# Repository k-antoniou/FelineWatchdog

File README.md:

# 🐱 Feline Watchdog: Missing Cat Alert System

Feline Watchdog is an ESP32-based system designed to monitor the Wi-Fi connection between your cat's collar-mounted ESP32 device and your home network. If the Wi-Fi connection is lost, indicating that your cat may have wandered out of range, the system sends a notification to your iOS or Android device using the ntfy Linux tool.

## Overview

Have you ever worried about your cat wandering too far from home? Feline Watchdog provides peace of mind by alerting you when your cat goes missing. By monitoring the Wi-Fi connection between your cat's collar-mounted ESP32 device and your home network, Feline Watchdog can detect when your cat is out of range and send you an alert notification on your mobile device.

## 🔧 Prerequisites

- ESP32 microcontroller
- Raspberry Pi (Optional)
- Docker (if using Raspberry Pi)
- Router (if not using Raspberry Pi)

## Embedded System Configuration

<p align="center">
  <b>Two implementations of Embedded System Configuration</b>
</p>

### Option 1: With Raspberry Pi

1. **Setting Up a Wi-Fi Hotspot on Embedded System**

   - For detailed instructions on setting up a Wi-Fi hotspot on your embedded system, please refer to the [Wi-Fi Hotspot Setup Instructions](WiFi_hotspot.md).

   - Use the provided bash script using the **nmcli** tool to create a Wi-Fi hotspot on the Raspberry Pi. 
    ```bash
    bash create_hotspot.sh
    ```
    or
    ```bash
    ./create_hotspot.sh
    ```
  2. **Install Docker on your Raspberry Pi**
  ```bash
  sudo docker --version
  Docker version 20.10.21, build 20.10.21-0ubuntu1~18.04.3
  ```
  ```bash
  docker run \
    -v /var/cache/ntfy:/var/cache/ntfy \
    -v /etc/ntfy:/etc/ntfy \
    -p 80:80 \
    -itd \
    binwiederhier/ntfy \
      serve \
      --cache-file /var/cache/ntfy/cache.db
  ```
## 📡 ESP32 Configuration and Notification Setup

### Option 1: Using Raspberry Pi as a Wi-Fi Hotspot

1. **ESP32 Configuration**
   - Upload the `cat.ino` code to your ESP32.
   - The ESP32 will connect to the Wi-Fi hotspot created by the Raspberry Pi.
   - Once connected, the assigned IP address will be printed to the serial monitor.

2. **Raspberry Pi Monitoring and Notification**
   - The Raspberry Pi continuously monitors the connection status of the ESP32.
   - If the connection is lost, it triggers a notification using ntfy.

### Option 2: Direct Connection to Router

For a basic example of using NTFY with ESP boards, check out the [ntfy_on_a_chip repository](https://github.com/gergepalfi/ntfy_on_a_chip). It provides a foundational setup for communicating with the NTFY server and can be adapted for various projects, including this.

1. **Connect ESP32 Directly to Router**
   - Configure your ESP32 to connect directly to your home Wi-Fi network (router).

2. **ESP32 Configuration**
   - Upload the `cat.ino` code to your ESP32.
   - The ESP32 will connect to the specified Wi-Fi network and print the assigned IP address to the serial monitor.

3. **Notification Setup**
   - Set up ntfy or another notification service on a server or computer within your home network.
   - This service will monitor the connection status of the ESP32.
   - If the connection is lost, it triggers a notification using ntfy or a similar service.

### Notes
- Ensure that your network's firewall settings allow communication between the ESP32 and the notification service.
- Configure ntfy or your chosen notification service according to the service's documentation for optimal performance.

## 🔩 PCB Design

  ### Dual Power Sources: Li-ion Battery and USB

  This setup allows the ESP32 to be powered either by a Li-ion battery or directly from a USB source via a voltage regulator.

  ### Li-ion Battery Connection
  - The Li-ion battery is connected to the **BATT+** and **BATT-** terminals of the charger module.
  - **BATT+** from the charger module is connected to the 3.3V input of the ESP32 through a Schottky diode.
  - **BATT-** is connected to the GND of the ESP32.

  ### USB Power Connection (For Re-programming)
  - The 5V line from the USB is connected to the **VIN** of the voltage regulator.
  - **GND** from the USB is connected to the GND of the voltage regulator.
  - The 3.3V output of the voltage regulator is connected to the 3.3V input of the ESP32 through a Schottky diode.

  Screenshots from KiCad:

  Screenshots from Fusion 360:

  ### Important Notes
  - Schottky diodes are used to prevent backfeeding between the battery and USB power sources.

  ## 🏗️ 3D Design

  Screenshots from Fusion 360:

  ## 3D Printed Case

  Screenshots of the printed 3D case:

  ## To Do

  - [x] Implement notification functionality using ntfy for sending alerts to iOS or Android devices.
  - [x] Implementation without a middle point such as Raspberry Pi, but directly with a router and ESP32.
  - [ ] Lower power consumption.
  - [ ] Implement HTTP communication method for sending alerts to a designated endpoint.
  - [ ] Implement MQTT communication method for publishing messages to a specific topic on an MQTT broker.
  - [ ] Ensure seamless integration of these functionalities within a Docker container on the Raspberry Pi.
  - [ ] Document setup and configuration steps for each notification method.
  - [ ] Test and validate the system's functionality across different scenarios.
  - [ ] Gather feedback and suggestions from users for further enhancements.

  ## 🧑‍💻 Authors

  - 

  - 

  ## 👥 Contributors

  Contributions are welcome! Feel free to submit pull requests or open issues if you encounter any problems.

   ## 🙏 Acknowledgements

   - A special thanks to the [ntfy_on_a_chip](https://github.com/gergepalfi/ntfy_on_a_chip) repository by [Gerge](https://github.com/gergepalfi). The example code and documentation provided were instrumental in implementing the direct connection option for the Feline Watchdog project. The guidance on using NTFY with ESP boards and the detailed explanation of HTTPS communication enabled us to streamline our setup by connecting the ESP32 directly to a router without needing an intermediate server like a Raspberry Pi. Your work greatly facilitated our development process and contributed to the success of the Feline Watchdog system. Thank you!

   - We would also like to acknowledge the creators of the [ntfy](https://ntfy.sh) app. The app’s simplicity and functionality made it easy to send and receive notifications, which is a core feature of the Feline Watchdog system. The ability to integrate it seamlessly into our project greatly enhanced its effectiveness.

   ## 📜 License
   
   This project is licensed under the [GPLv3 License](https://opensource.org/licenses/GPL-3.0) - see the [LICENSE](LICENSE) file for details.

   - 

**Thank you for visiting FelineWatchdog!** ✨

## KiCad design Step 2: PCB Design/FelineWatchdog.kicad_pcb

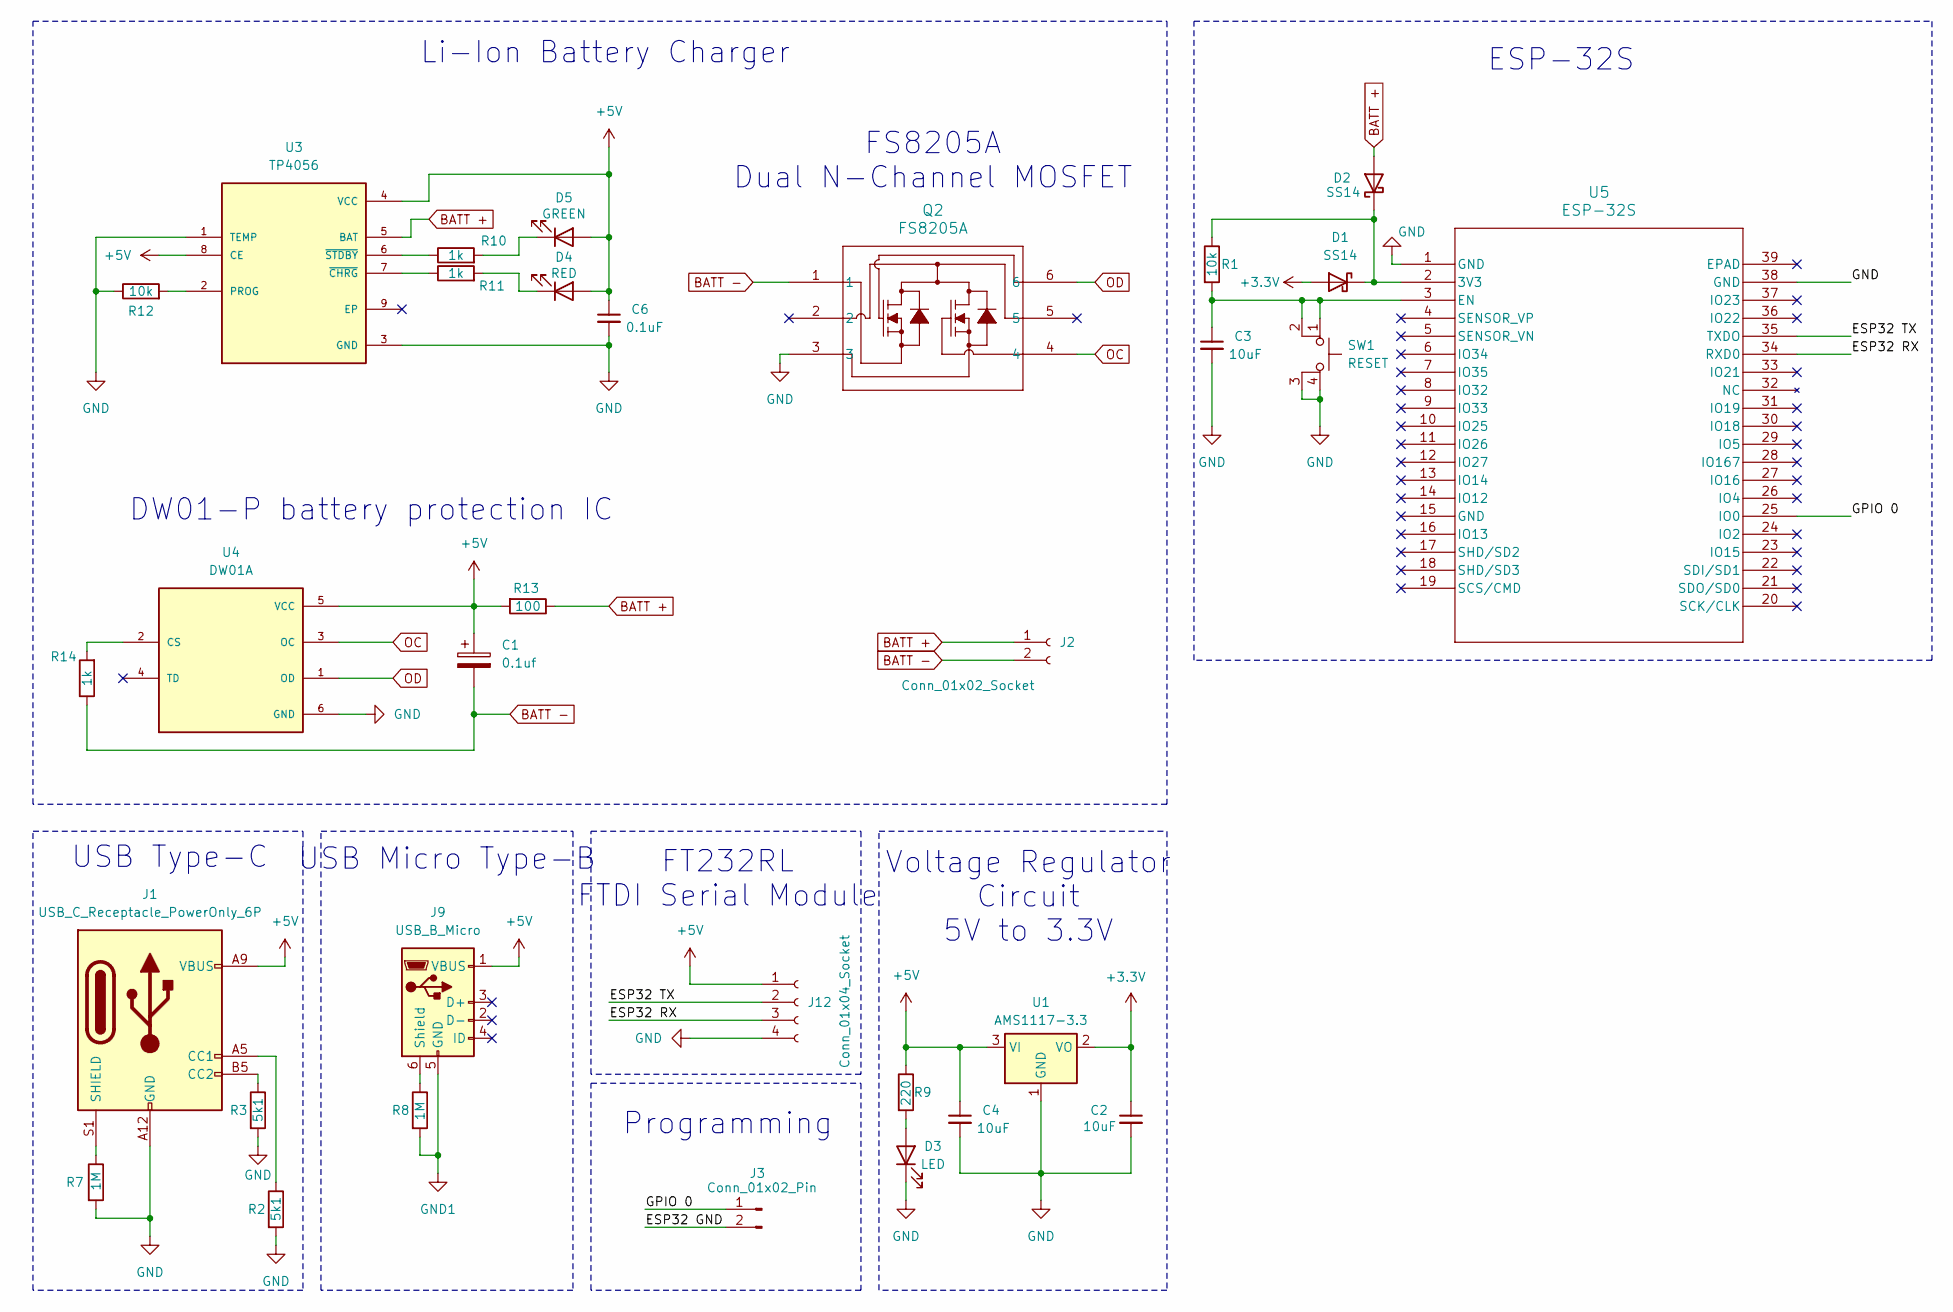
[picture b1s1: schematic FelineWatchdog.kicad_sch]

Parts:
C1: 0.1uf; CP_EIA-1608-08_AVX-J
C2, C3, C4: 10uF; C_0805_2012Metric_Pad1.18x1.45mm_HandSolder
C6: 0.1uF; C_0603_1608Metric_Pad1.08x0.95mm_HandSolder
D1, D2: SS14; D_SMA_Handsoldering
D3: LED; LED_0805_2012Metric_Pad1.15x1.40mm_HandSolder
D4: RED; LED_0805_2012Metric_Pad1.15x1.40mm_HandSolder
D5: GREEN; LED_0805_2012Metric_Pad1.15x1.40mm_HandSolder
J1: USB_C_Receptacle_PowerOnly_6P; USB_C_Receptacle_GCT_USB4125-xx-x-0190_6P_TopMnt_Horizontal
J2: Conn_01x02_Socket; JST_EH_S2B-EH_1x02_P2.50mm_Horizontal
J3: Conn_01x02_Pin; PinHeader_1x02_P1.00mm_Horizontal
J9: USB_B_Micro; USB_Micro-B_Amphenol_10118194_Horizontal
J12: Conn_01x04_Socket; PinHeader_1x04_P1.00mm_Horizontal
Q2: FS8205A; SOT-23-6L_TCP-L
R1, R12: 10k; R_0805_2012Metric_Pad1.20x1.40mm_HandSolder
R2, R3: 5k1; R_0805_2012Metric_Pad1.20x1.40mm_HandSolder
R7, R8: 1M; R_0805_2012Metric_Pad1.20x1.40mm_HandSolder
R9: 220; R_0805_2012Metric_Pad1.20x1.40mm_HandSolder
R10, R11: 1k; R_0805_2012Metric_Pad1.20x1.40mm_HandSolder
R13: 100; R_0805_2012Metric_Pad1.20x1.40mm_HandSolder
R14: 1k; R_0805_2012Metric
SW1: RESET; MySwitch_SW_SPST_PTS647_Sx50
U1: AMS1117-3.3; SOT-223-3_TabPin2
U3: TP4056; SOP127P600X175-9N
U4: DW01A; SOT95P280X145-6N; PARTREV 1.8
U5: ESP-32S; ESP-32S_AIT

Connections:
+3.3V: C2.1, D1.2 (A), U1.2 (VO)
+5V: C1.1, C4.1, C6.1, D4.2 (A), D5.2 (A), J1.A9 (VBUS), J1.B9 (VBUS), J9.1 (VBUS), J12.1, R9.1, R13.2, U1.3 (VI), U3.4 (VCC), U3.8 (CE), U4.5 (VCC)
/ESP32 RX: J12.3, U5.34 (RXD0)
/ESP32 TX: J12.2, U5.35 (TXDO)
/GPIO 0: J3.1, U5.25 (IO0)
BATT +: D2.2 (A), J2.1, R13.1, U3.5 (BAT)
BATT -: C1.2, J2.2, Q2.1, R14.1
unnamed: D1.1 (K), D2.1 (K), R1.1, U5.2 (3V3)
unnamed: D3.2 (A), R9.2
unnamed: D4.1 (K), R11.2
unnamed: D5.1 (K), R10.2
unnamed: J1.A5 (CC1), R2.1
unnamed: J1.B5 (CC2), R3.1
unnamed: J1.S1 (SHIELD), R7.1
unnamed: J9.5 (GND), R8.2
unnamed: J9.6 (Shield), R8.1
unnamed: R12.2, U3.2 (PROG)
unnamed: R11.1, U3.7 (~CHRG)
unnamed: R10.1, U3.6 (~STDBY)
unnamed: R14.2, U4.2 (CS)
unnamed: C3.1, R1.2, SW1.1, SW1.2, U5.3 (EN)
OC: Q2.4, U4.3 (OC)
OD: Q2.6, U4.1 (OD)

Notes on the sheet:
ESP-32S
DW01-P battery protection IC
FS8205A Dual N-Channel MOSFET
FT232RL FTDI Serial Module
Voltage Regulator Circuit 5V to 3.3V
Li-Ion Battery Charger
USB Type-C
USB Micro Type-B
Programming

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
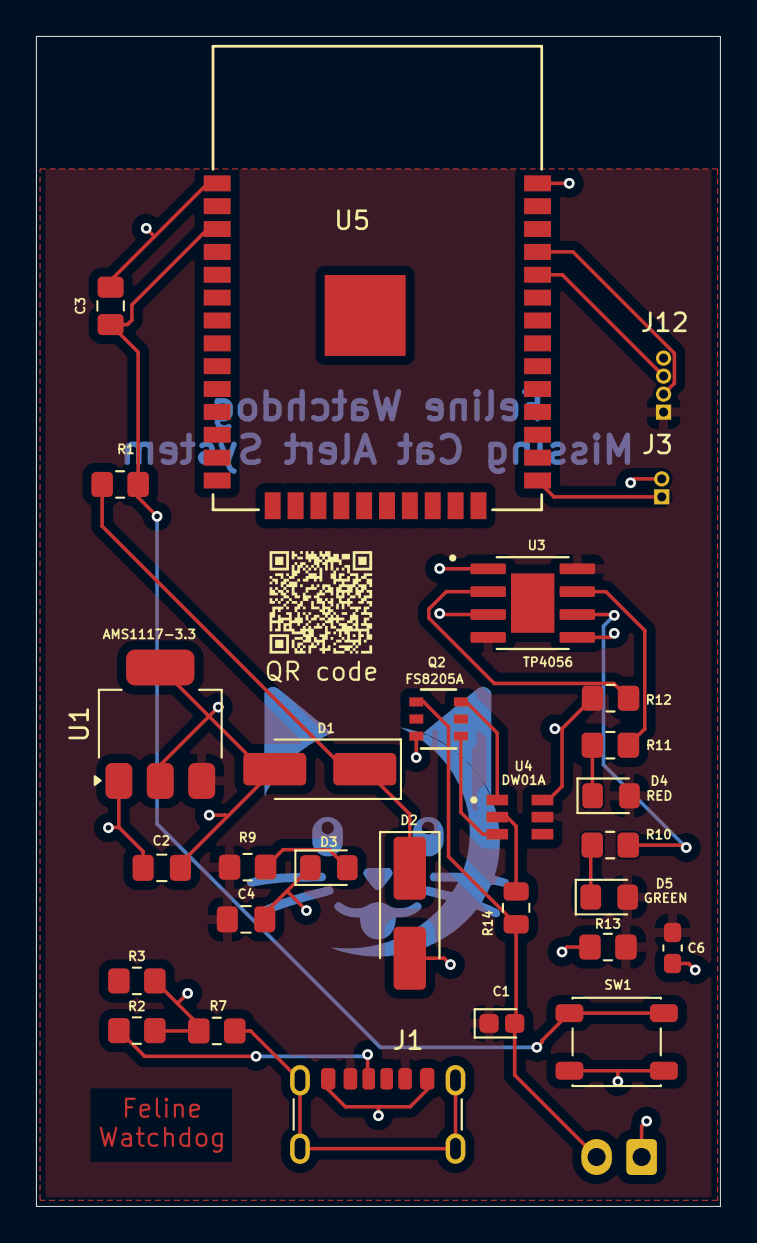
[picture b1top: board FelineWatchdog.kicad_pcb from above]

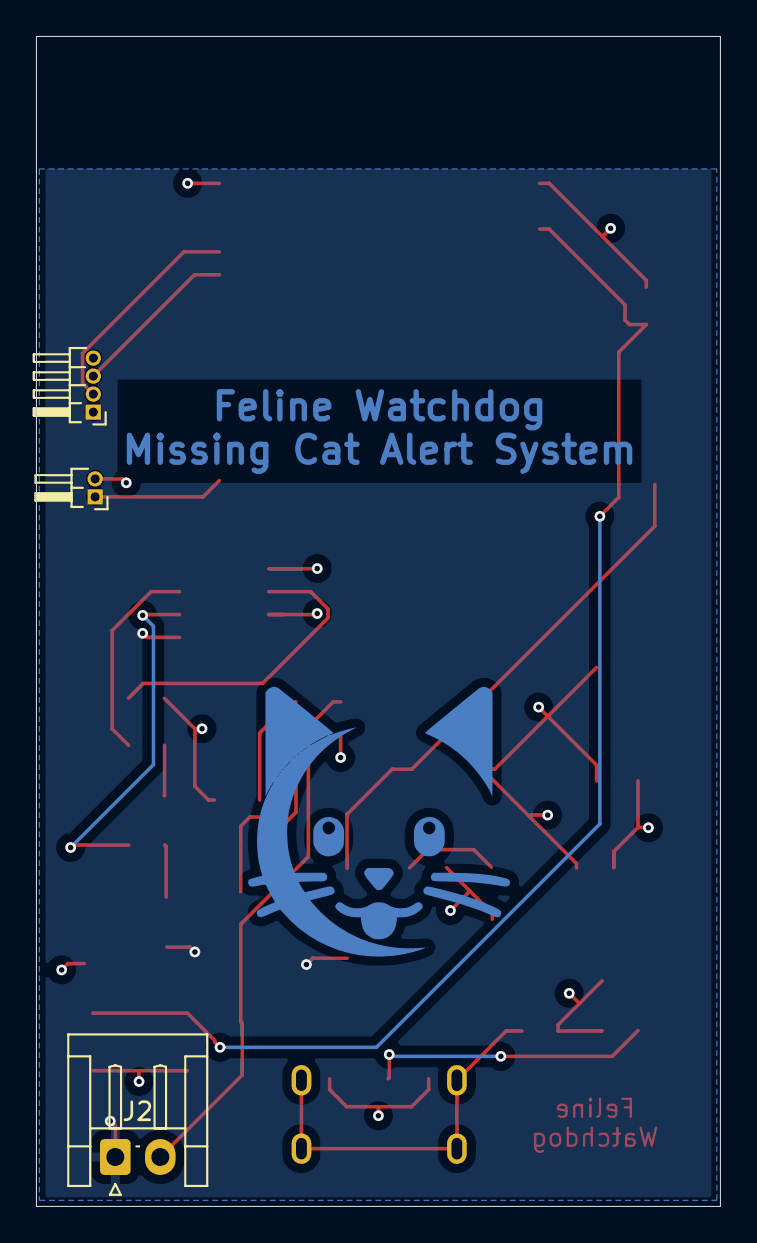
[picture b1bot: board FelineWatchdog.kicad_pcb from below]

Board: 4 copper layers, 38.0 x 65.0 mm, 32 parts (4 on the bottom side), 22 nets.

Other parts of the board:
G1: LOGO; cat
G2: LOGO; QRcat

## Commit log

2024-05-02 Added bash script to create Wi-Fi hotspot
2024-05-03 Initial project version: initial commit
2024-05-03 Added new ProjectImage.png
2024-07-04 Modified
2024-08-05 Remove outdated files and directories; add new design files
2024-08-05 Add implementation for direct connection to router with ESP32
2024-08-10 Fix license mismatch: Update from MIT to GPLv3
    The project was incorrectly redistributing GPLv3-licensed code under the MIT license. This commit updates the project to correctly reflect the GPLv3 license, ensuring compliance with its terms.
    Changes include:
    Updated license text to GPLv3
    Changed license badge to GPLv3
    Corrected license details in documentation
    See the LICENSE file for full GPLv3 details.
2024-08-10 Add reference to Wi-Fi hotspot setup instructions in README.md
2024-11-09 Switch to 4-layer PCB stackup with dedicated power and ground planes
    - **Top Layer**: Filled zone for **BAT+** (Battery Positive).
    - **Inner Layer 1**: 3.3V power plane for ESP32 and low-voltage components.
    - **Inner Layer 2**: Shared **GND** plane with **BAT-** (Battery Negative).
    - **Bottom Layer**: Additional **BAT+** power distribution.
    Inner layers ensure stable power delivery, improved signal integrity, and reduced EMI.
2025-01-17 Added .gitignore for KiCad PCB project to exclude temporary and exported files

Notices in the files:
README.md:
License: GPLv3
